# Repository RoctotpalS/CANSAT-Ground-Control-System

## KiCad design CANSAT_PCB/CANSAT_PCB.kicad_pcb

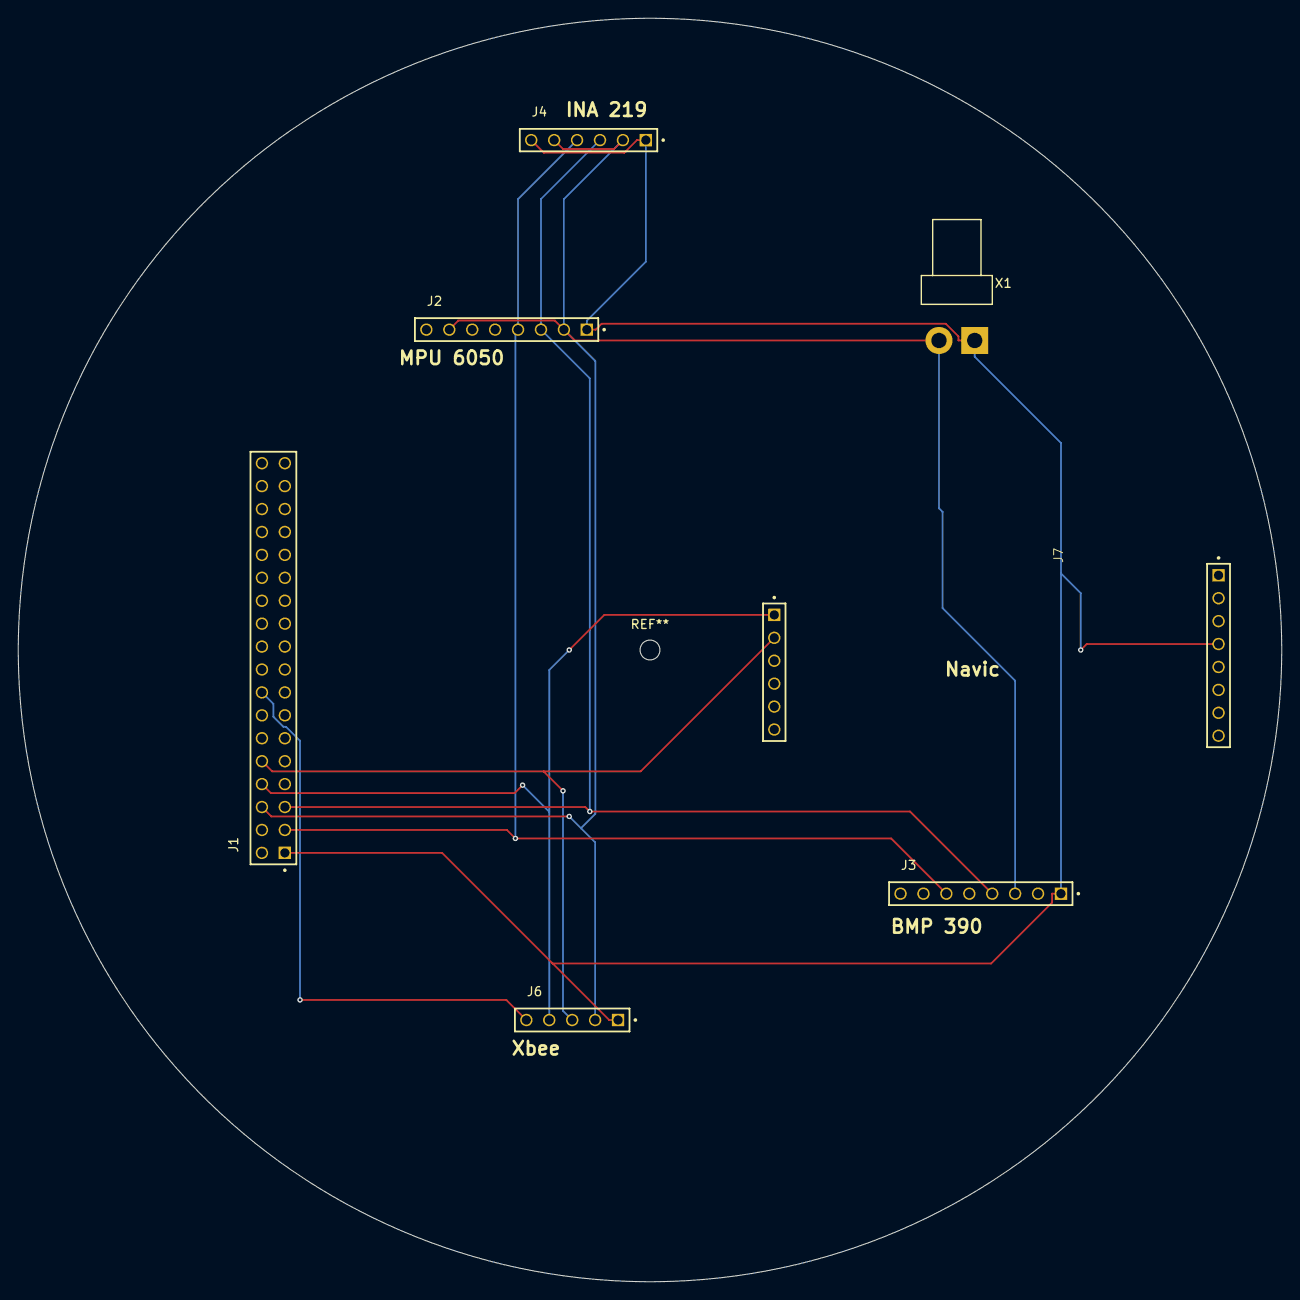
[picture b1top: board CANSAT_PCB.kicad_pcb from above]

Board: 2 copper layers, 140.0 x 140.0 mm, 7 parts (0 on the bottom side), 7 nets.

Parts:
J1: MTSW-118-06-G-D-050
J2, J3: MTSW-108-09-T-S-525; SAMTEC_MTSW-108-09-T-S-525
J4: HTSW-106-20-SM-S; SAMTEC_HTSW-106-20-SM-S
J6: MTSW-105-24-L-S-252; SAMTEC_MTSW-105-24-L-S-252
J7: TSW-114-29-T-S; navic
X1: B2PS-VH

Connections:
unnamed: J1.01, J2.01, J3.01, J4.01, J4.06, J6.01, J7.10, X1.1
unnamed: J1.03, J2.04, J3.06, J4.04
unnamed: J1.05, J2.03, J3.04, J4.03
unnamed: J1.06, J2.02, J2.07, J3.03, J4.02, J4.05, J6.02, X1.2
unnamed: J1.08, J6.04, J7.01
unnamed: J1.10, J6.03, J7.02
unnamed: J1.16, J6.05
